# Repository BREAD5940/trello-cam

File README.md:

# frc-autocam

> **Moved (2026-11-19).** AutoCAM now lives in [BREAD5940/bread-server](https://github.com/BREAD5940/bread-server)
> under `apps/autocam`, with this repo's history. Its service runs on the team server and Fusion's add-in on the
> laptop; pushing bread-server `main` deploys both. This repo is archived and read-only; make changes there.

Trello cards with Onshape part links → nested, CAM'd sheets in Fusion → WinCNC `.tap` files back on Trello
for the team's ShopSabre 23. A human reviews every sheet before it is cut.

- `docs/BRIEF.md`: the settled decisions.
- `docs/PLAN.md`: architecture and milestones.
- `docs/STATUS.md`: where things stand and what's still untested.
- `CLAUDE.md`: the hard rules.

## Development (WSL)

The repo lives on the Windows drive (`C:\dev\frc-autocam`, `/mnt/c/dev/frc-autocam` from WSL) so Fusion can
load `fusion/` directly. Keep the venv in the WSL home, not in the repo.

```bash
python3 -m venv ~/.venvs/frc-autocam
~/.venvs/frc-autocam/bin/pip install -e ".[dev]"
~/.venvs/frc-autocam/bin/pytest                                 # fully offline; network is blocked in tests
~/.venvs/frc-autocam/bin/python -m autocam_service config-check
```

Secrets go in `.env` (copy `.env.example`), which is gitignored.

## Layout

| Path | What |
|---|---|
| `core/autocam_core/` | pure logic, standard library only (also imported inside Fusion) |
| `service/autocam_service/` | the Windows service: Trello, Onshape, hot folder |
| `fusion/` | Fusion scripts and add-in, the pinned post, tool library, and templates |
| `config/autocam.toml` | all settings, in inches; `[assumed]` lists values still to confirm |
| `tests/` | pytest suite |

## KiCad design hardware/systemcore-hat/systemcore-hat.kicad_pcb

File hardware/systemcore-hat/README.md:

# SystemCore lever hat

A 2-layer PCB that presses onto the top of a Limelight SystemCore and turns every Molex SL port
(5× CAN, 6× SmartIO, 2× I2C, RSL) plus the BRIDGE power/CAN port into WAGO lever terminals, one
lever per wire. Ethernet, the four USB-A ports and the USB-C LINK port stay usable through cut-outs.
Nothing latches: the hat holds by friction on 38 gold contacts, plus the four corner screws if you
run them through it (recommended on a robot).

**Status: designed and checked in CAD only. Not built, not tested.** Read "Check before ordering".

| | |
|---|---|
|  |  |

## How it works

- **Underneath:** 14 single-row 2.54 mm female headers, 11.0 mm tall, gold. SystemCore's SL headers
  (Molex 171971) are shrouded 0.65 mm square pins at 2.54 mm. The socket drops into the shroud's
  3.07 mm wide cavity and bottoms on its floor. That gives 6.1 mm of pin engagement and puts the hat's
  underside 0.5 mm above SystemCore's tallest rim.
- **On top:** WAGO 2601-11xx lever terminal blocks (3.5 mm pitch, 26–16 AWG, wire enters from the
  board edge, lever on top), in two strips that overhang SystemCore's long edges.
- **BRIDGE (Micro-Fit+):** Molex doesn't make a board-mount mate for Micro-Fit+. It also carries
  SystemCore's main power. So it is wired with a short pigtail cut from an official Micro-Fit+ device
  cable: the pigtail plugs into BRIDGE through the window and is soldered to the hat. This one
  connection does latch.
- **Electrically** the hat is a pure 1:1 pass-through. Every lever connects only to its own SystemCore
  pin; no grounds are tied together and there are no components.

## Lever map

Groups are numbered left to right with Ethernet on the right. Check them against the numbers
printed on your SystemCore. Pin order and colours come from Limelight's *FIRST Control System Cable
Specifications* rev 1.

| Hat label | SystemCore port | Levers, left to right as you read the labels |
|---|---|---|
| CAN 0 … CAN 4 | CAN buses (SL 2-pin) | H = CAN high (yellow), L = CAN low (green) |
| BRIDGE | BRIDGE, Micro-Fit+ (via pigtail) | H, L, + = power in, G = ground |
| RSL | RSL (SL 2-pin) | G, + = 10 V switched |
| IO 0 … IO 5 | SmartIO (SL 3-pin) | G = ground, V = 3.3 V out, S = signal |
| I2C 0, I2C 1 | I2C (SL 4-pin) | G, V = 3.3 V, D = SDA, C = SCL |

## Check before ordering

1. **CAN latch side (assumption).** Limelight's simplified STEP draws the five CAN headers as plain
   blocks, so their orientation isn't visible. Every SL header whose orientation *is* visible (SmartIO,
   I2C, RSL) has its latch ramp facing the Ethernet side, and the hat assumes the CAN headers do too.
   Look at your SystemCore. The latch side of an SL header is the wider wall with the slot the cable's
   latch clicks into. If the CAN ones face away from Ethernet, set `CAN_LATCH_SIDE = -1` in
   `gen_hat.py` and regenerate (below). If you don't, CAN H and L land 1.5 mm off and the hat won't seat.
2. **1:1 paper check.** Print `fab/check-print-1to1.pdf` at 100 % (no "fit to page"). The board is
   135.5 mm wide; measure it on the print. Lay it on the SystemCore, outline to outline. Every socket
   pad should sit over a header pin, and the Ethernet, USB, display and BRIDGE/LINK cut-outs should
   line up.
3. **Socket height.** The sockets are hanxia `HX PM2.54-1xNP ZC H11` (LCSC C41427517/18/19), listed as
   11.0 mm. I couldn't get their datasheet. A taller socket is fine: the hat just sits higher, so use
   thicker spacers. A socket under about 10.6 mm makes the hat rest on SystemCore's rims before the
   sockets bottom out, which still gives about 5.7 mm of engagement. Any 2.54 mm female header with an
   11 mm insulator and a 2.5 mm wide body works; use gold (SystemCore's pins are gold).

## Ordering (JLCPCB or PCBWay)

Upload `fab/systemcore-hat-gerbers.zip`.

| Setting | Value |
|---|---|
| Layers | 2 |
| Size | 135.5 × 100.6 mm |
| Thickness | 1.6 mm (the stack height assumes it) |
| Copper | **2 oz recommended** if SystemCore is powered through BRIDGE (1 oz works; see limits) |
| Min track / space / hole | 0.3 / 0.2 / 1.0 mm. No vias. |
| Finish, colour | anything |

All parts are through-hole and easy to hand-solder (about 125 joints). For JLC THT assembly, use
`fab/bom-jlc.csv` and `fab/cpl-jlc.csv` and check every part's rotation in their preview. At the time
of writing JLC had no stock of WAGO 2601-1104, and DigiKey and Mouser stock all three sizes.

### Parts (per hat)

| Qty | Refs | Part | LCSC |
|---|---|---|---|
| 6 | J1–J6 | Female header 1×2, 2.54 mm, 11 mm, gold (hanxia HX PM2.54-1x2P ZC H11) | C41427517 |
| 6 | J7–J12 | Female header 1×3, same series | C41427518 |
| 2 | J13–J14 | Female header 1×4, same series | C41427519 |
| 6 | TB1–TB5, TB7 | WAGO 2601-1102 | C7509568 |
| 6 | TB8–TB13 | WAGO 2601-1103 | C7472698 |
| 3 | TB6, TB14, TB15 | WAGO 2601-1104 | C7472748 |
| ½ | J15 | Official Micro-Fit+ device cable `MFP-R-4_MFP-R-4_DEVICE_300mm`, cut in half (one cable makes two pigtails) | – |
| 4 | – | 2.0 mm spacers or washers for M4/#8, plus screws 2 mm + 1.6 mm longer than your current ones | – |
| 1 | – | Small zip tie (≤ 2.5 mm) | – |

## Assembly

1. **Sockets (underside).** Insert J1–J14 from the bottom (the side with the SystemCore outline) and
   solder on top. Keep them square to the board. Optional, for perfect alignment: put the sockets in
   the hat, press the hat onto an **unpowered** SystemCore, tack one pin per socket, then take it off
   and finish soldering.
2. **Levers (top).** TB1–TB15 go on the top with the wire openings facing out over the board edges.
   Solder underneath.
3. **BRIDGE pigtail.** Cut the device cable in half and strip 3 mm. Push the wires into J15 from the
   top: YEL → H, GRN → L, RED → +, BLK → G. Solder underneath, trim flush, and zip-tie the bundle
   through the two small holes. Leave enough slack to reach BRIDGE through the window.
4. **Continuity.** Check each lever against its SystemCore-side socket contact (42 circuits), and check
   neighbouring levers for shorts.

## Installing

1. Unplug everything from SystemCore's SL ports and BRIDGE.
2. Put a 2.0 mm spacer on each corner screw hole. If your sockets differ, seat the hat first and
   measure the gap.
3. Press the hat straight down. The sockets centre themselves on the pins and stop on the header floors.
4. Plug the pigtail into BRIDGE through the window.
5. Run longer screws through the hat, spacers and SystemCore into the robot.

Wires: strip 8–9 mm, lift the lever, insert, close. 26–16 AWG; FIRST's SL cables are 22 AWG.
Ferrules 0.25–0.75 mm² work.

## Limits and notes

- **Fit is from CAD.** The fit is checked against Limelight's `SYSTEMCORE_SIMPLIFIED_STEP.step`
  (2026-11-19) and Molex drawing 1719710000-SD. `fit_check.py` confirms that only the sockets enter
  SystemCore, that every socket clears its cavity walls by 0.28 mm or more, and that nothing else
  collides.
- **Power through BRIDGE.** Power runs through two lever poles (UL 10 A) and 1.5 mm traces about
  3 cm long. Those traces are good for about 3 A at a 10 °C rise on 1 oz copper, or about 5 A on
  2 oz. SystemCore is rated 40 W max, which is 3.3 A at 12 V and more during brownouts; hence 2 oz.
- **Footprint and height.** The hat is 135.5 × 100.6 mm. It overhangs SystemCore by 13.8 mm on the
  CAN side and 15.4 mm on the SmartIO side. It stands 39.5 mm above SystemCore's base with levers
  closed, and about 48 mm with a lever open.
- **Ports not converted.** USB-A, USB-C LINK and Ethernet are left alone; their data lines can't go
  through lever terminals. The display, status LEDs and the round light pipe stay visible.
- **Rules.** Check the 2027 robot rules for anything about control-system wiring before competing
  with it.

## Regenerating

Everything is scripted. Edit the constants at the top of `gen_hat.py` and rerun:

```sh
/usr/bin/python3 gen_hat.py                                   # KiCad 9's python: board + build/systemcore-hat.dsn
cd build && java -jar freerouting-2.1.0.jar -de systemcore-hat.dsn -do systemcore-hat.ses -mp 40 && cd ..
/usr/bin/python3 -c "import pcbnew; b=pcbnew.LoadBoard('systemcore-hat.kicad_pcb'); \
  pcbnew.ImportSpecctraSES(b,'build/systemcore-hat.ses'); pcbnew.SaveBoard('systemcore-hat.kicad_pcb',b)"
kicad-cli pcb drc systemcore-hat.kicad_pcb                    # expect 0 violations, 0 unconnected
python make_models.py                                         # envelope 3D models (needs cadquery-ocp)
kicad-cli pcb export step --subst-models --user-origin 150x150mm -f -o build/systemcore-hat.step systemcore-hat.kicad_pcb
python fit_check.py SYSTEMCORE_SIMPLIFIED_STEP.step build/systemcore-hat.step --render renders
/usr/bin/python3 make_fab.py                                  # gerbers zip, BOM, CPL, 1:1 print
```

The board coordinates are SystemCore's own, from the STEP: origin at the box centre, +X toward
Ethernet, +Y toward the CAN row. In KiCad they sit at offset (150, 150) with y flipped.

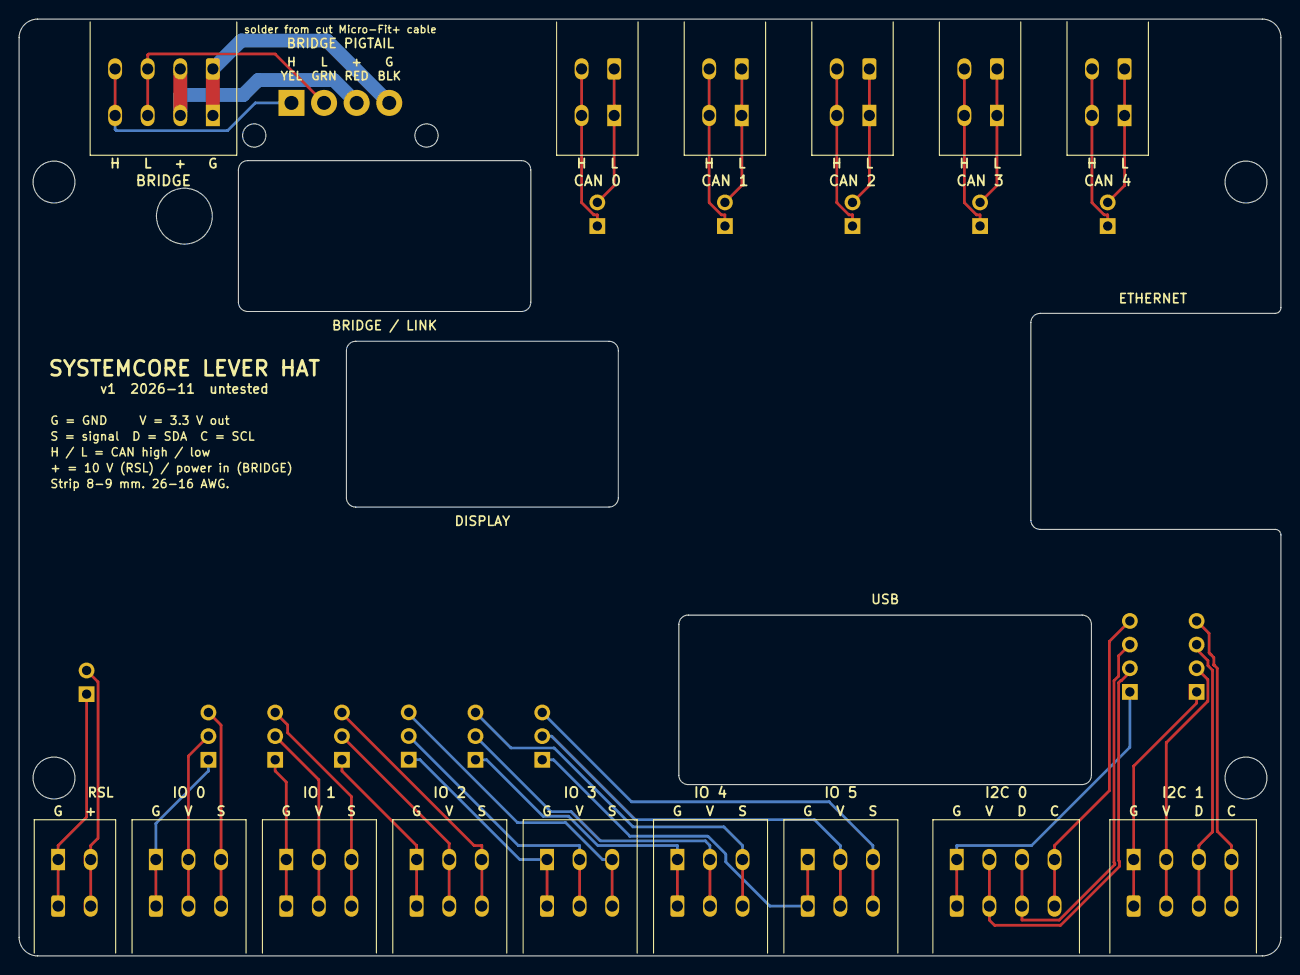
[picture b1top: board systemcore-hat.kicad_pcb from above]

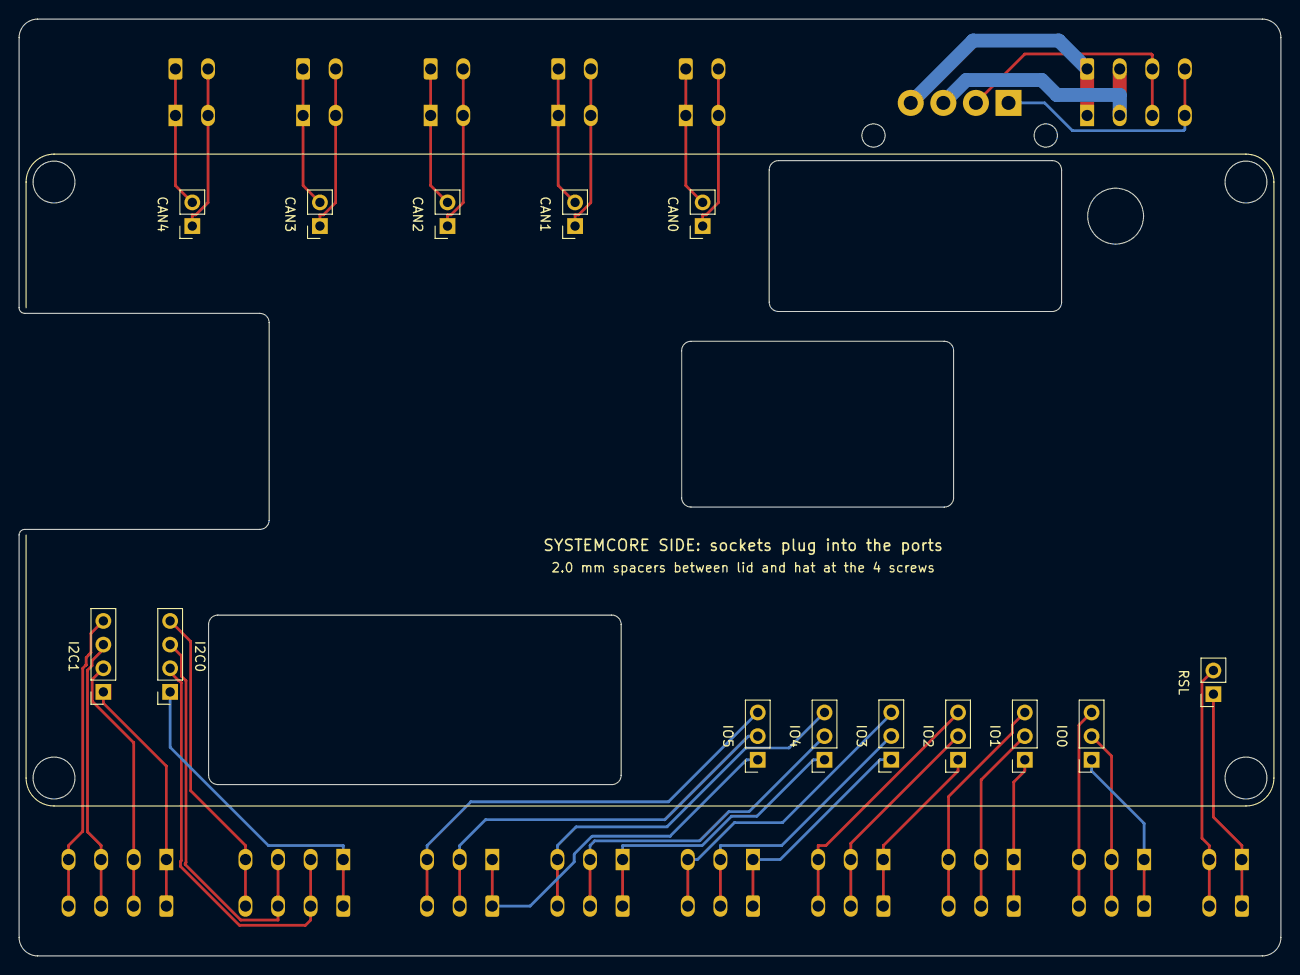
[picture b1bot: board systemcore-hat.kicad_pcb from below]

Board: 2 copper layers, 135.5 x 100.6 mm, 36 parts (14 on the bottom side), 42 nets.

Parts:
H1, H2, H3, H4: M4/#8 screw; MountingHole_4.5mm_Head8mm
H5, H6: zip tie; ZipTie_Hole_2.5mm
J1, J2, J3, J4, J5, J6: 1x2 H11; PinSocket_1x02_P2.54mm_Vertical
J7, J8, J9, J10, J11, J12: 1x3 H11; PinSocket_1x03_P2.54mm_Vertical
J13, J14: 1x4 H11; PinSocket_1x04_P2.54mm_Vertical
J15: BRIDGE pigtail; Pigtail_1x04_P3.5mm_D1.5mm
TB1, TB2, TB3, TB4, TB5, TB7: WAGO 2601-1102; TerminalBlock_WAGO_2601-1102_1x02_P3.50mm_Horizontal
TB6, TB14, TB15: WAGO 2601-1104; TerminalBlock_WAGO_2601-1104_1x04_P3.50mm_Horizontal
TB8, TB9, TB10, TB11, TB12, TB13: WAGO 2601-1103; TerminalBlock_WAGO_2601-1103_1x03_P3.50mm_Horizontal

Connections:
BR_CANH: J15.1, TB6.4
BR_CANL: J15.2, TB6.3
BR_GND: J15.4, TB6.1
BR_VIN: J15.3, TB6.2
CAN0_H: J1.1, TB1.2
CAN0_L: J1.2, TB1.1
CAN1_H: J2.1, TB2.2
CAN1_L: J2.2, TB2.1
CAN2_H: J3.1, TB3.2
CAN2_L: J3.2, TB3.1
CAN3_H: J4.1, TB4.2
CAN3_L: J4.2, TB4.1
CAN4_H: J5.1, TB5.2
CAN4_L: J5.2, TB5.1
I2C0_3V3: J13.2, TB14.2
I2C0_GND: J13.1, TB14.1
I2C0_SCL: J13.4, TB14.4
I2C0_SDA: J13.3, TB14.3
I2C1_3V3: J14.2, TB15.2
I2C1_GND: J14.1, TB15.1
I2C1_SCL: J14.4, TB15.4
I2C1_SDA: J14.3, TB15.3
IO0_3V3: J7.2, TB8.2
IO0_GND: J7.1, TB8.1
IO0_SIG: J7.3, TB8.3
IO1_3V3: J8.2, TB9.2
IO1_GND: J8.1, TB9.1
IO1_SIG: J8.3, TB9.3
IO2_3V3: J9.2, TB10.2
IO2_GND: J9.1, TB10.1
IO2_SIG: J9.3, TB10.3
IO3_3V3: J10.2, TB11.2
IO3_GND: J10.1, TB11.1
IO3_SIG: J10.3, TB11.3
IO4_3V3: J11.2, TB12.2
IO4_GND: J11.1, TB12.1
IO4_SIG: J11.3, TB12.3
IO5_3V3: J12.2, TB13.2
IO5_GND: J12.1, TB13.1
IO5_SIG: J12.3, TB13.3
RSL_10V: J6.2, TB7.2
RSL_GND: J6.1, TB7.1

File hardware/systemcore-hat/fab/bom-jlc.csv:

Comment,Designator,Footprint,LCSC Part #
hanxia HX PM2.54-1x2P ZC H11,"J1,J2,J3,J4,J5,J6",PinSocket_1x02_P2.54mm_Vertical,C41427517
hanxia HX PM2.54-1x3P ZC H11,"J7,J8,J9,J10,J11,J12",PinSocket_1x03_P2.54mm_Vertical,C41427518
hanxia HX PM2.54-1x4P ZC H11,"J13,J14",PinSocket_1x04_P2.54mm_Vertical,C41427519
WAGO 2601-1102,"TB1,TB2,TB3,TB4,TB5,TB7",TerminalBlock_WAGO_2601-1102_1x02_P3.50mm_Horizontal,C7509568
WAGO 2601-1104,"TB6,TB14,TB15",TerminalBlock_WAGO_2601-1104_1x04_P3.50mm_Horizontal,C7472748
WAGO 2601-1103,"TB8,TB9,TB10,TB11,TB12,TB13",TerminalBlock_WAGO_2601-1103_1x03_P3.50mm_Horizontal,C7472698
